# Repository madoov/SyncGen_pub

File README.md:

# SyncGen_pub
Outlay sync generator

OUTLAW ビデオ信号ジェネレータの公開用リポジトリです。
昔のパソコン・ゲーム機・アーケード基板の映像信号のタイミングを、ドットクロックから同期の形まで設定して出力する、Efinix Trion T20Q144 の基板です。

## 中身

| フォルダ | 内容 |
| --- | --- |
| `rtl/` | FPGA の RTL (Verilog-2001、Efinity)。トップは `video_gen_top.v`。`*.hex` は文字列・フォント・プリセットの ROM、`timing.sdc` はタイミング制約 |
| `docs/` | 取扱説明書 [`manual.md`](docs/manual.md) と PDF 版 [`SyncGen.pdf`](docs/SyncGen.pdf)、ピン配置 [`pinout.md`](docs/pinout.md) (RTL のポート ⇔ 回路図のネット ⇔ FPGA のピン) |
| `pcb/` | KiCad 10 のプロジェクト (回路図・基板) |
| `efinity/` | Efinity のプロジェクト (`OUTLAW_video_signa_gen.xml`、Interface Designer のピン設定 `.peri.xml`)。プロジェクトは RTL を `../../RTL/` から読む (Windows の Efinity 用) |

## ライセンス

BSD 3-Clause License ([`LICENSE`](LICENSE))。無保証です。

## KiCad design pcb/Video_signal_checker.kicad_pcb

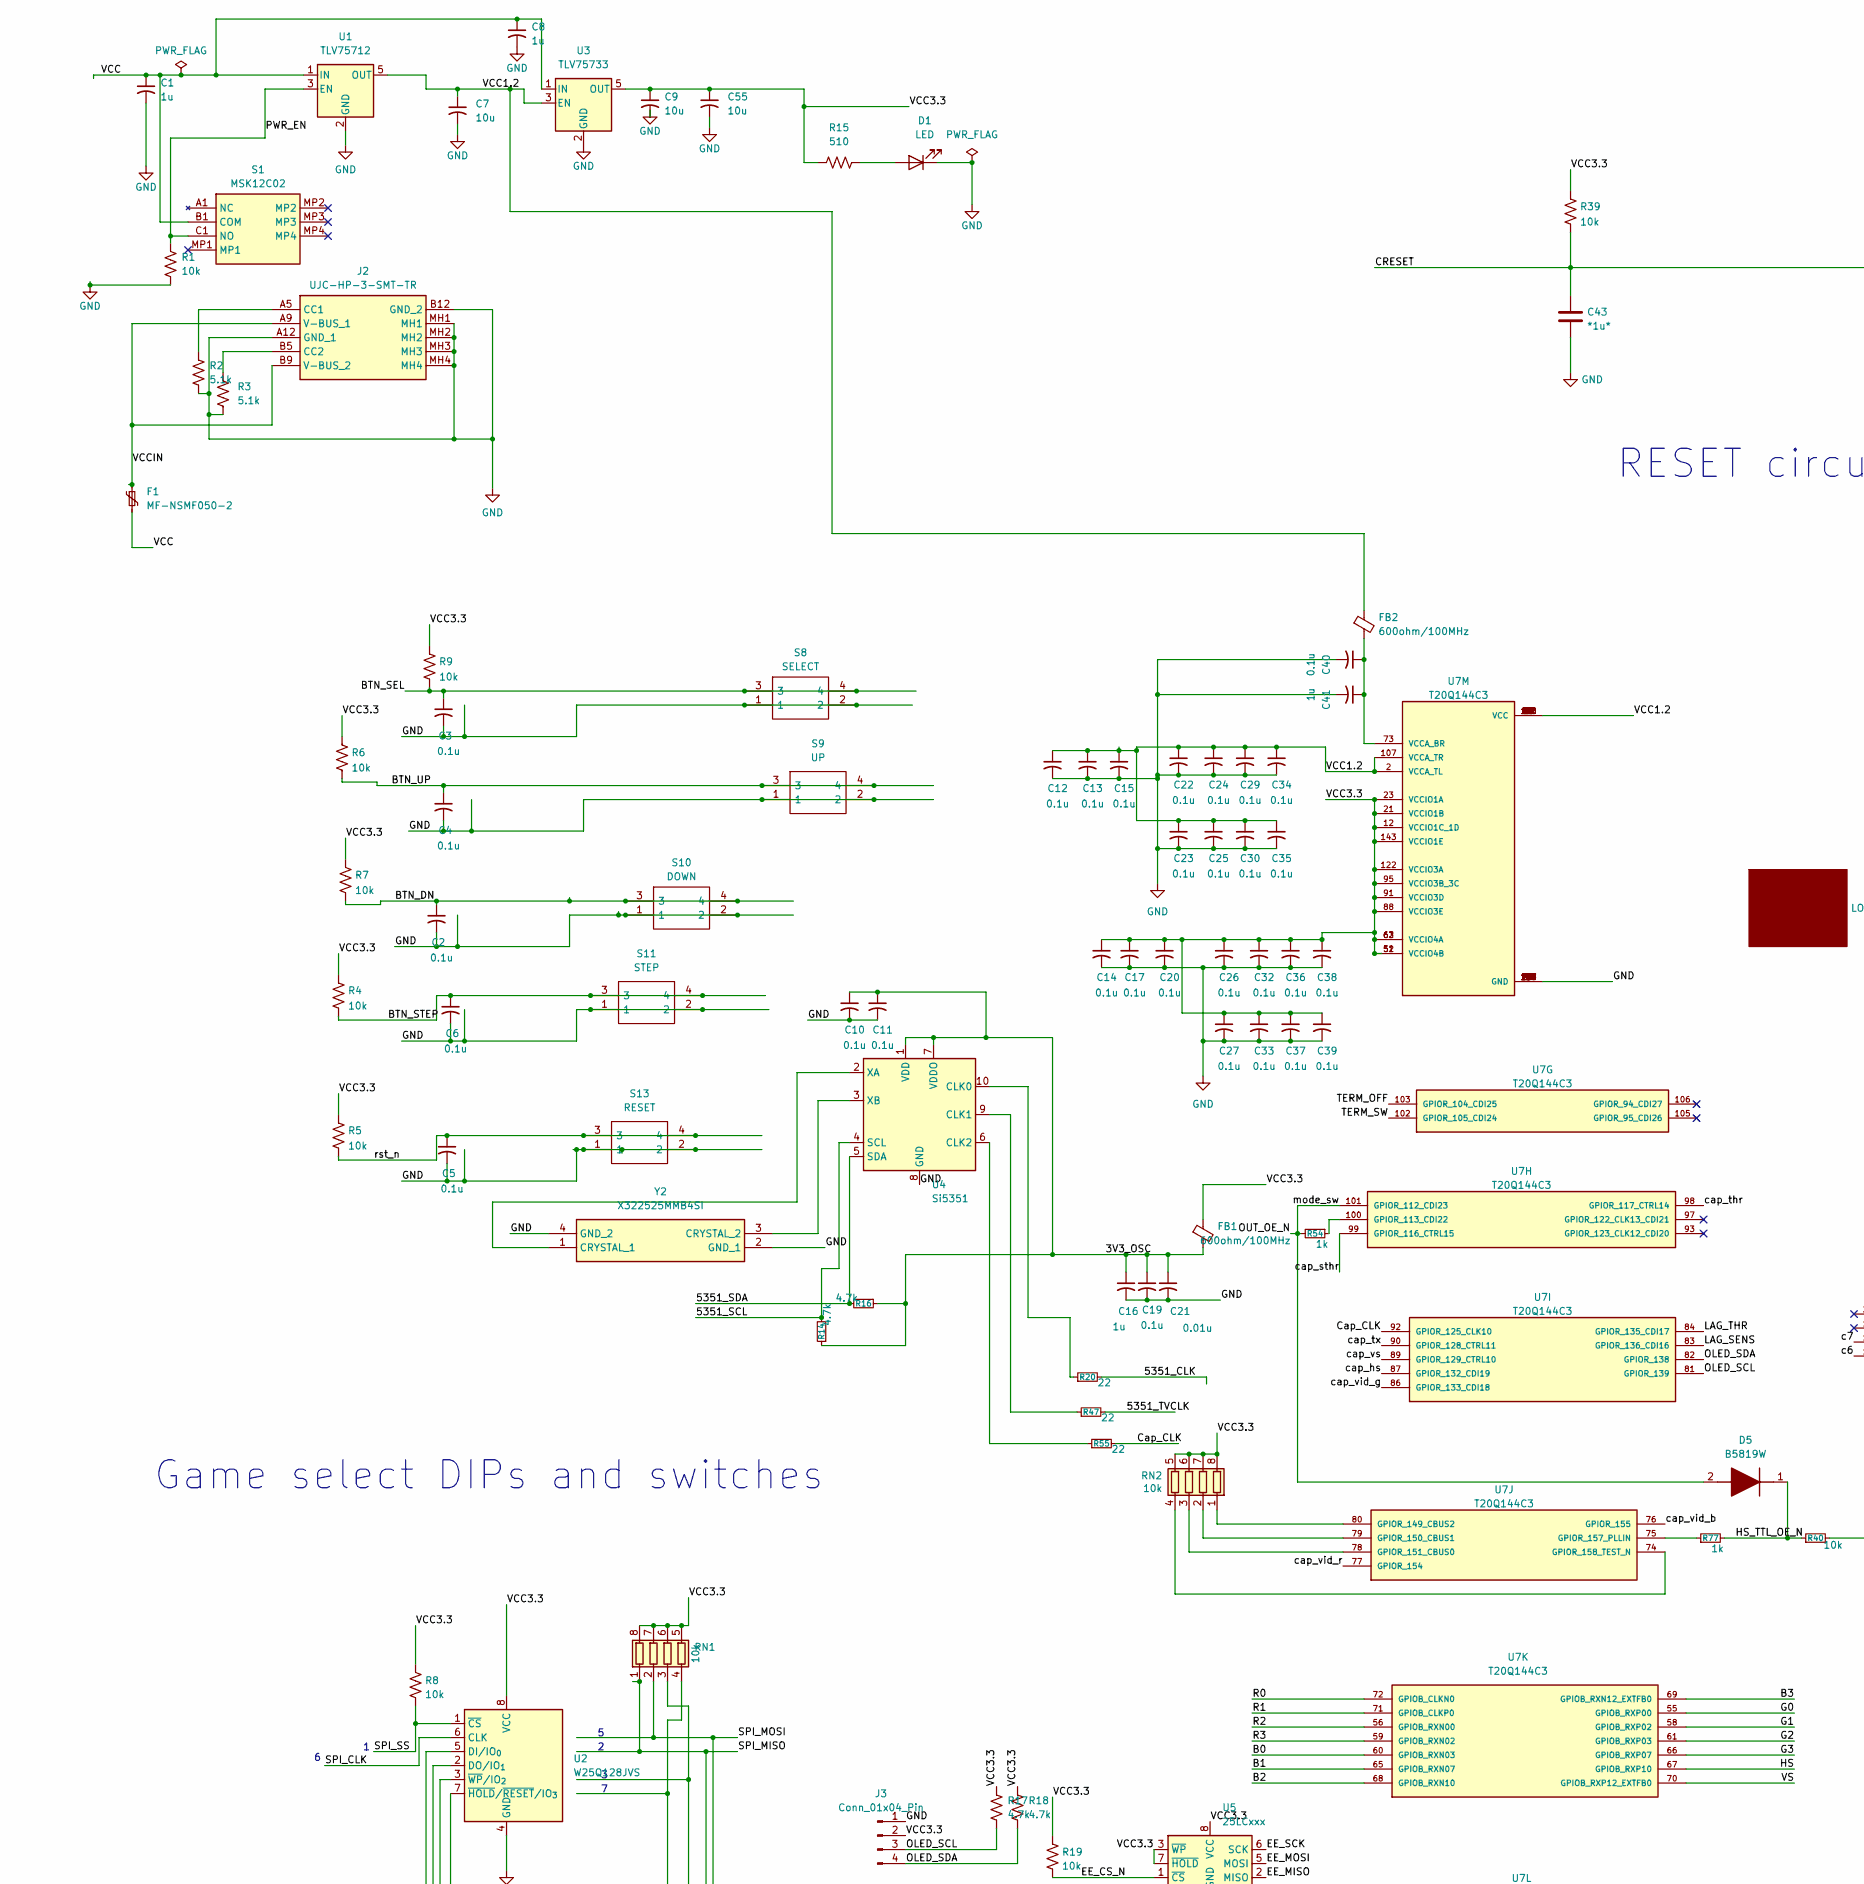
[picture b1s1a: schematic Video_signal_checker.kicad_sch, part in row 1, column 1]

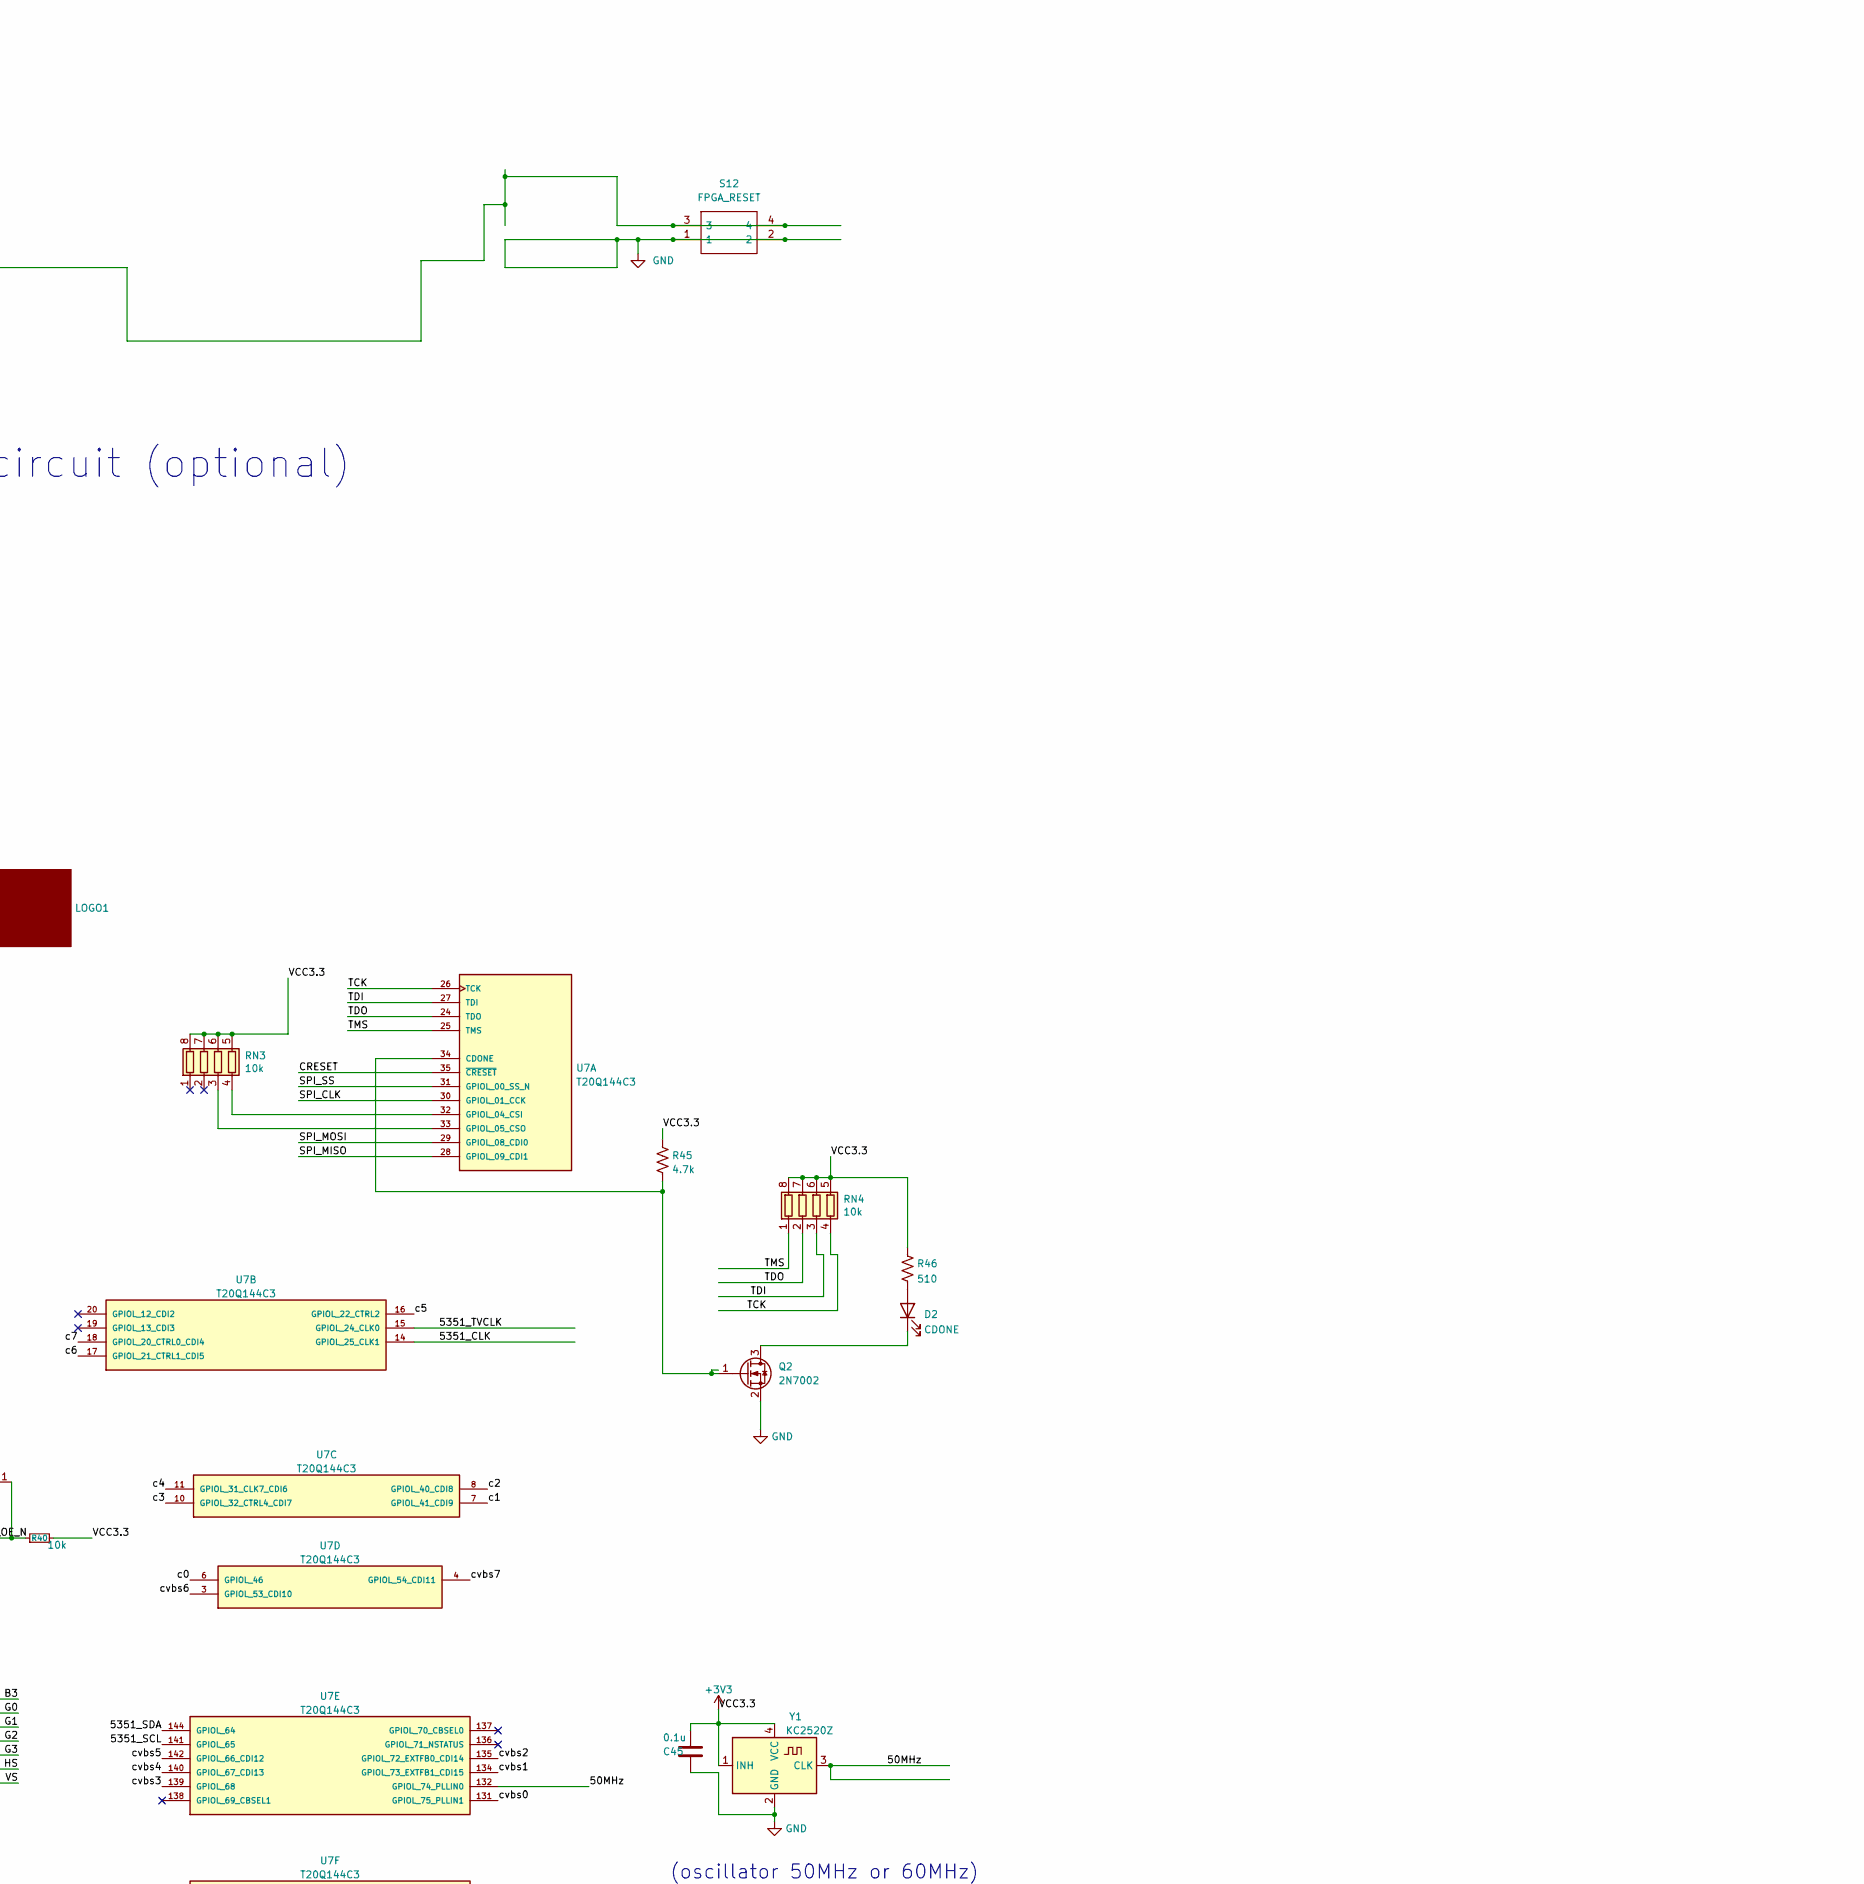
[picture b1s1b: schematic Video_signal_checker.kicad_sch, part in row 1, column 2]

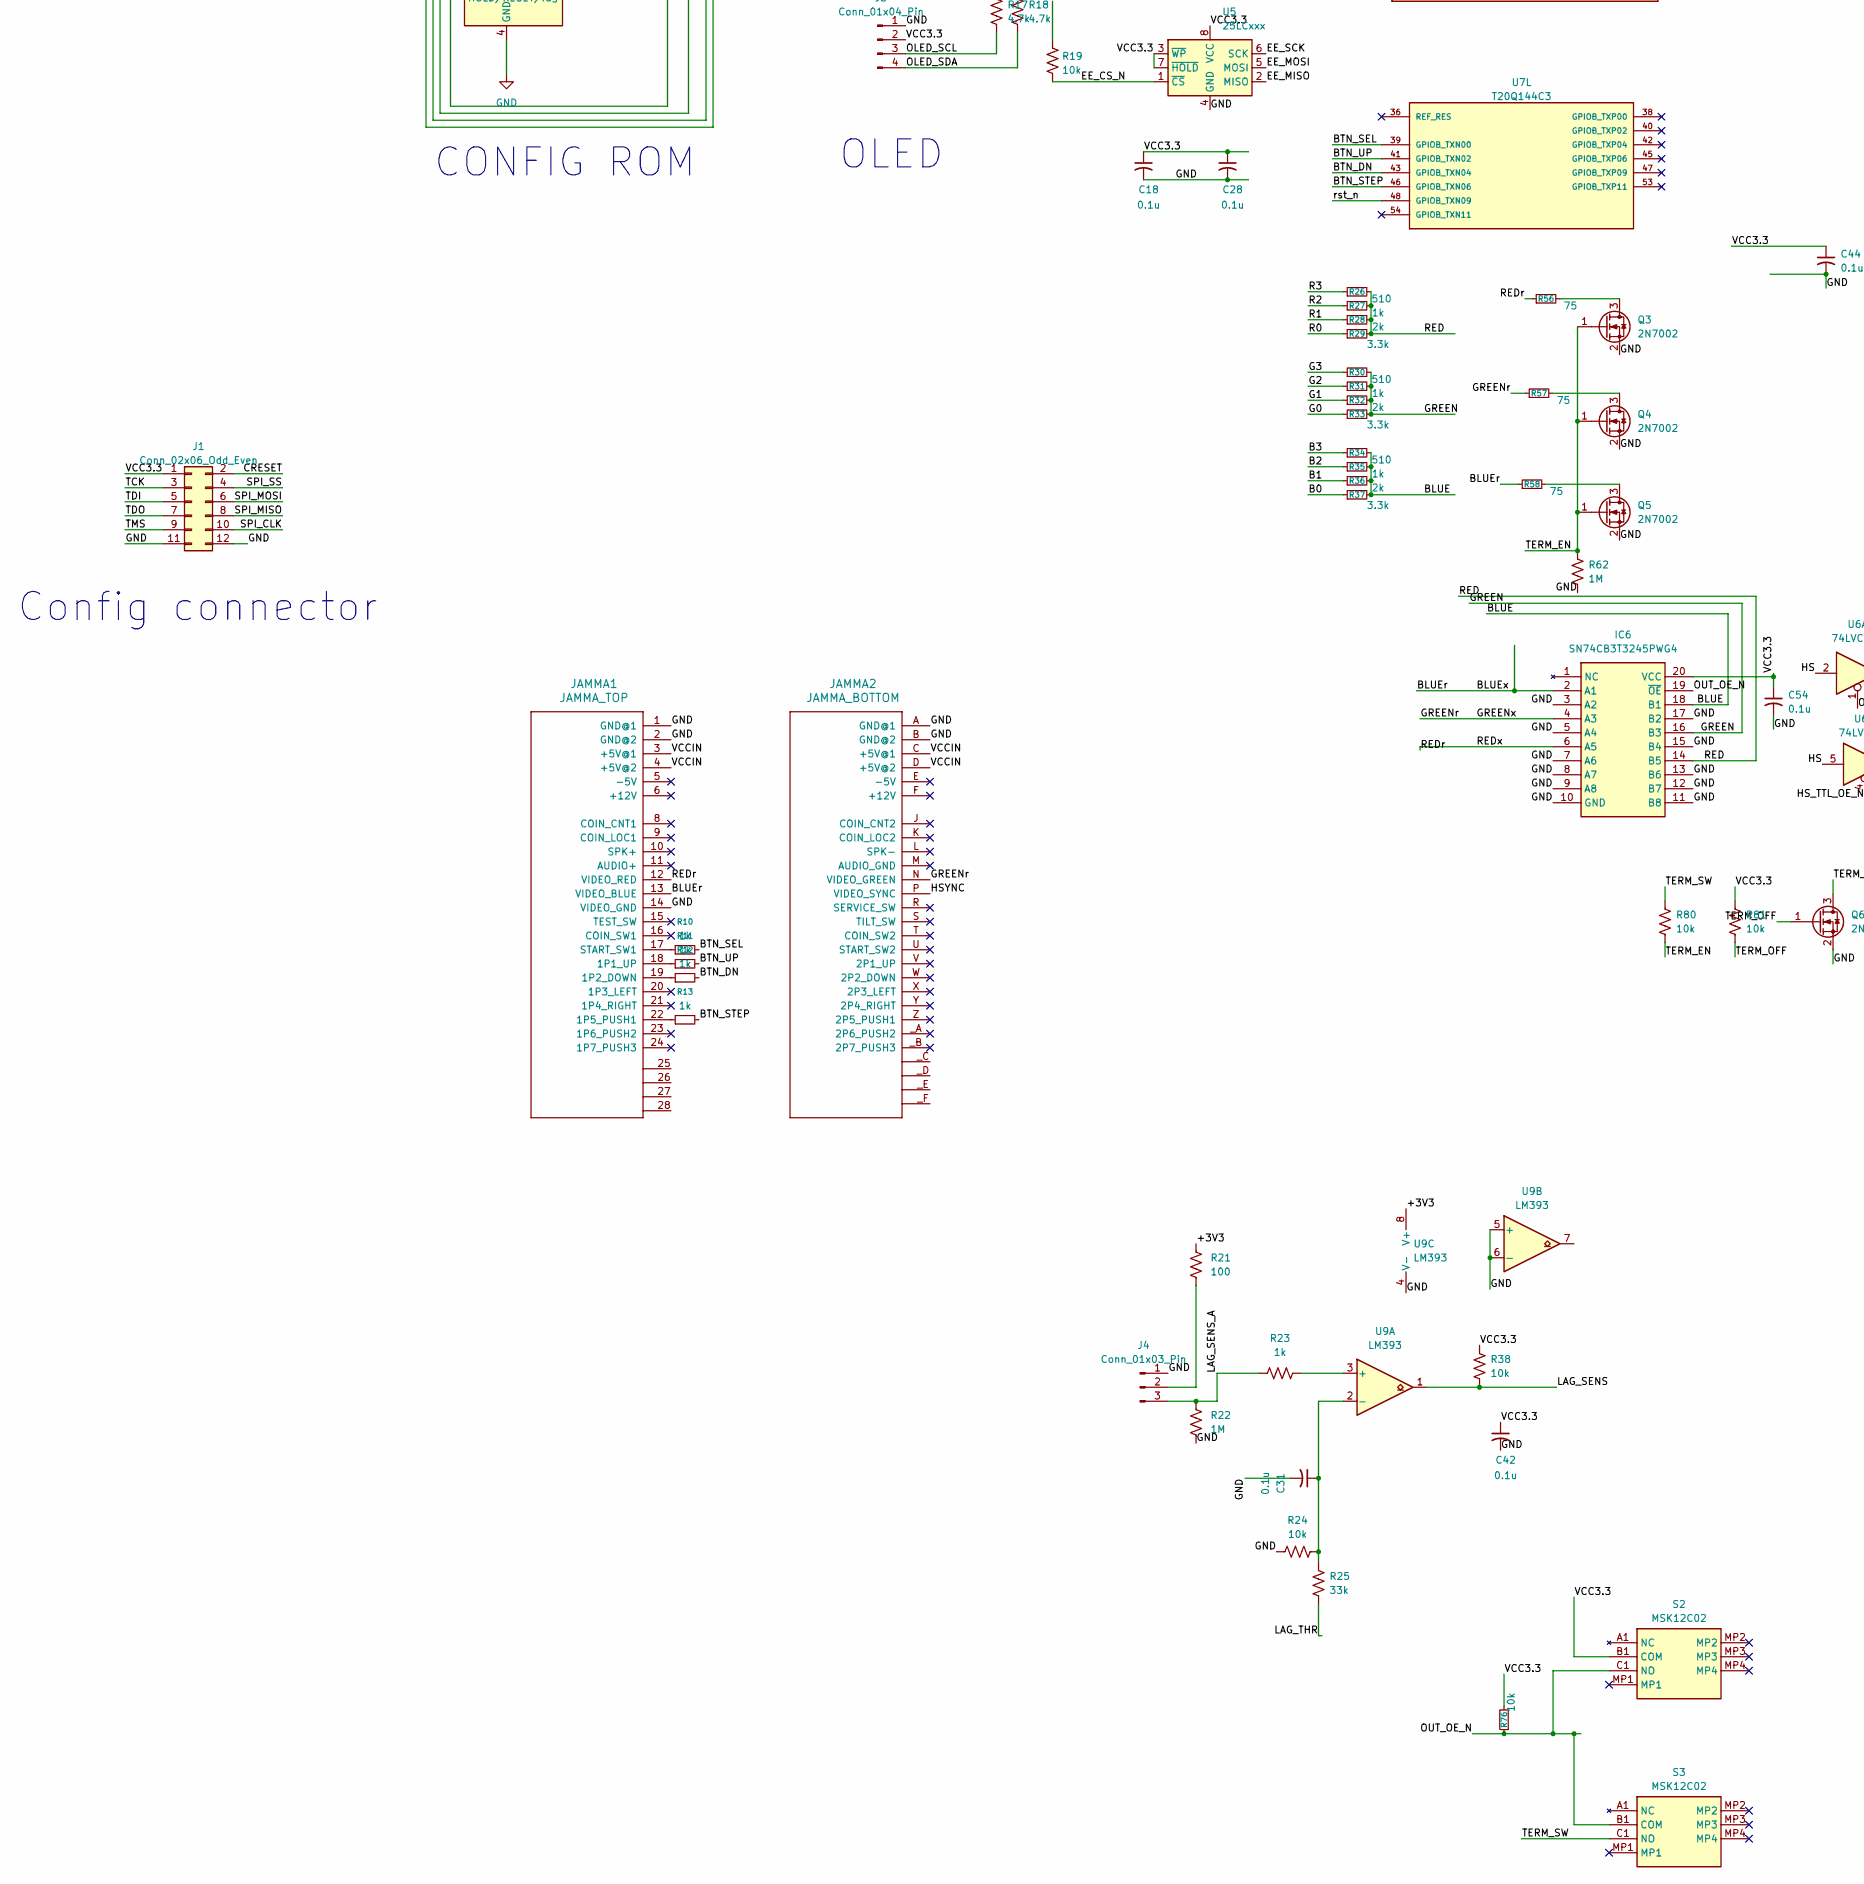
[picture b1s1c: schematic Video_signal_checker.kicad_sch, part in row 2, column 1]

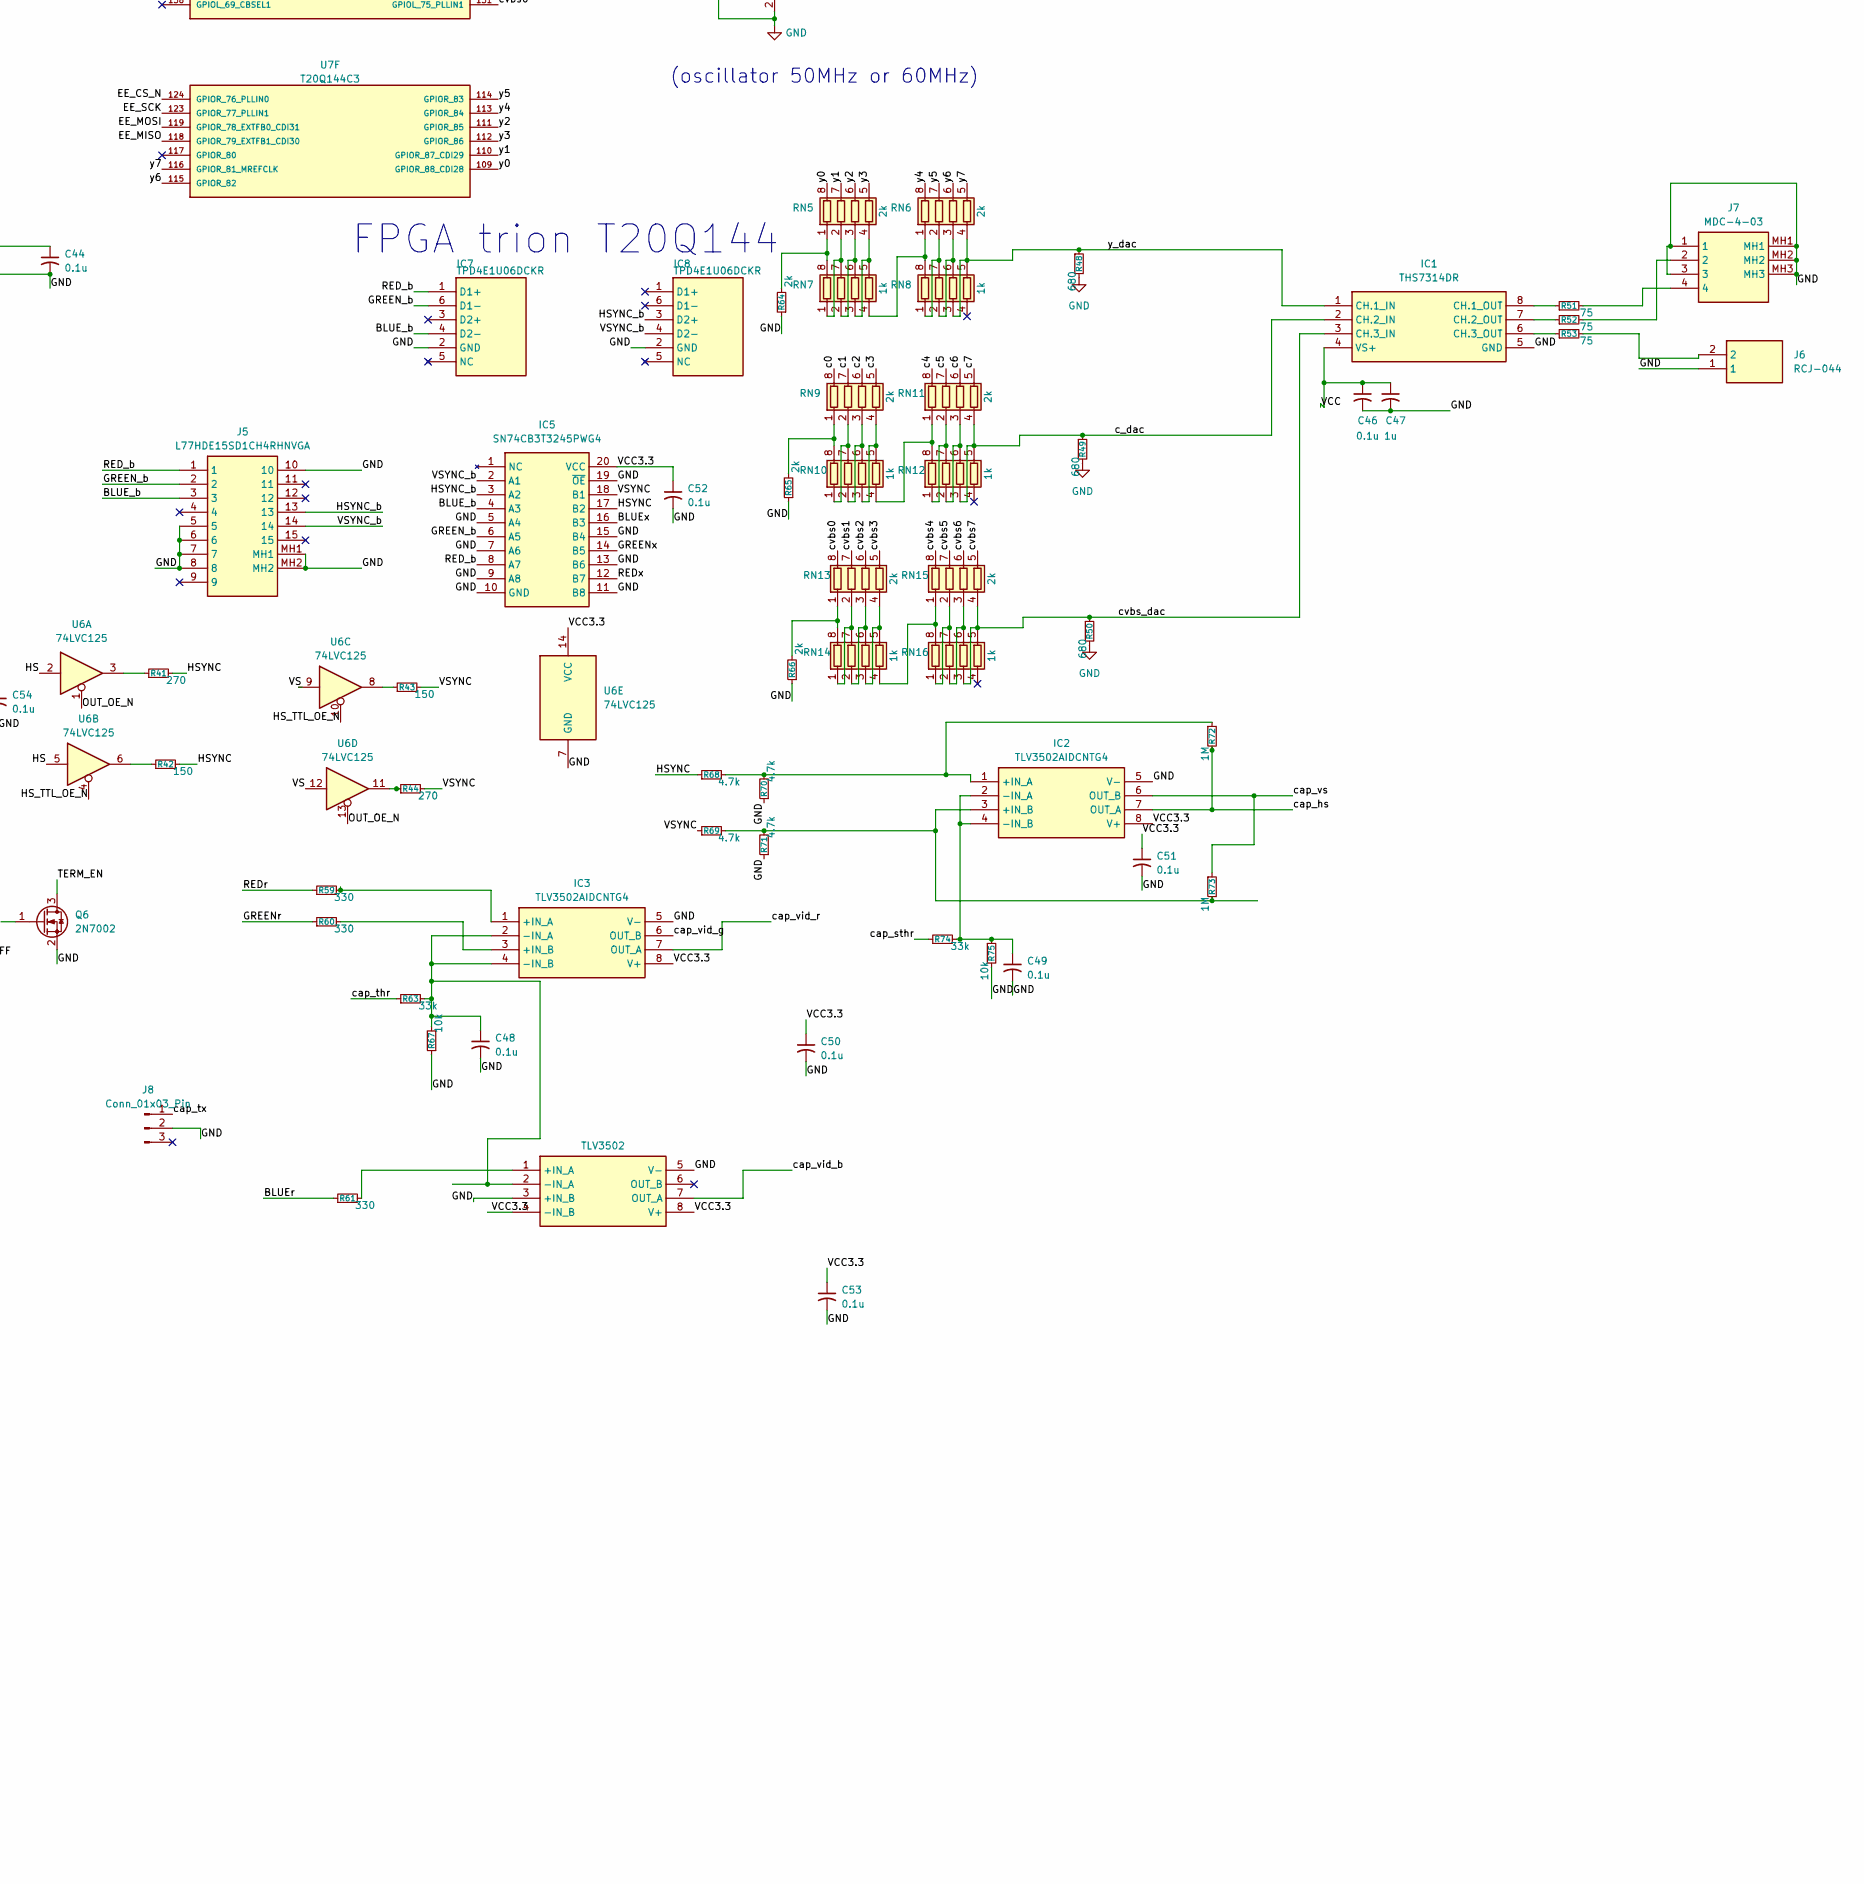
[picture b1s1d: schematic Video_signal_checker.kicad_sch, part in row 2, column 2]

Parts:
C1, C8, C16, C41, C47: 1u; C_0402_1005Metric_Pad0.74x0.62mm_HandSolder; LCSC C52923
C2, C3, C4, C5, C6, C10, C11, C12, C13, C14, C15, C17, C18, C19, C20, C22, C23, C24, C25, C26, C27, C28, C29, C30, C31, C32, C33, C34, C35, C36, C37, C38, C39, C40, C42, C44, C45, C46, C48, C49, C50, C51, C52, C53, C54: 0.1u; C_0402_1005Metric_Pad0.74x0.62mm_HandSolder; LCSC C1525
C7, C9, C55: 10u; C_0603_1608Metric_Pad1.08x0.95mm_HandSolder; LCSC C19702
C21: 0.01u; C_0402_1005Metric_Pad0.74x0.62mm_HandSolder; LCSC C15195
C43: *1u*; C_0402_1005Metric_Pad0.74x0.62mm_HandSolder; LCSC C52923
D1: LED; LED_0603_1608Metric_Pad1.05x0.95mm_HandSolder; LCSC C2286
D2: CDONE; LED_0603_1608Metric_Pad1.05x0.95mm_HandSolder; LCSC C2286
D5: B5819W; SOD3716X125N; Manufacturer_Part_Number B5819W; LCSC C8598
F1: MF-NSMF050-2; Fuse_1206_3216Metric_Pad1.42x1.75mm_HandSolder; LCSC C883126
FB1, FB2: 600ohm/100MHz; L_0603_1608Metric_Pad1.05x0.95mm_HandSolder; LCSC C1002
IC1: THS7314DR; SOIC127P600X175-8N; Manufacturer_Part_Number THS7314DR; Mouser Part Number 595-THS7314DR
IC2, IC3: TLV3502AIDCNTG4; SOT65P280X145-8N; Manufacturer_Part_Number TLV3502AIDCNTG4; Mouser Part Number 595-TLV3502AIDCNTG4
IC4: TLV3502; SOT65P280X145-8N; Manufacturer_Part_Number TLV3502AIDCNTG4; Mouser Part Number 595-TLV3502AIDCNTG4
IC5, IC6: SN74CB3T3245PWG4; SOP65P640X120-20N; Manufacturer_Part_Number SN74CB3T3245PWG4; Mouser Part Number 595-SN74CB3T3245PWG4
IC7, IC8: TPD4E1U06DCKR; SOT-363_SC-70-6; LCSC C194628
J1: Conn_02x06_Odd_Even; PinSocket_2x06_P2.54mm_Vertical
J2: UJC-HP-3-SMT-TR; UJCHP3SMTTR; Manufacturer_Part_Number UJC-HP-3-SMT-TR; Mouser Part Number 490-UJC-HP-3-SMT-TR
J3: Conn_01x04_Pin; PinSocket_1x04_P2.54mm_Vertical
J4, J8: Conn_01x03_Pin; PinHeader_1x03_P2.54mm_Vertical
J5: L77HDE15SD1CH4RHNVGA; Manufacturer_Part_Number L77HDE15SD1CH4RHNVGA; Mouser Part Number 523-7HDE15SDH4RHNVGA
J6: RCJ-044; RCJ044; Manufacturer_Part_Number RCJ-044; Mouser Part Number 490-RCJ-044
J7: MDC-4-03; MDC403; Manufacturer_Part_Number MDC-4-03
JAMMA1: JAMMA_TOP; JAMMA_TOP_10cm
JAMMA2: JAMMA_BOTTOM; JAMMA_BOTTOM_10cm
LOGO1: logo-mini
Q2, Q3, Q4, Q5, Q6: 2N7002; SOT-23; LCSC C8545
R1, R4, R5, R6, R7, R8, R9, R19, R24, R38, R39, R40, R67, R75, R76, R80, R81: 10k; R_0402_1005Metric_Pad0.72x0.64mm_HandSolder; LCSC C25744
R2, R3: 5.1k; R_0402_1005Metric_Pad0.72x0.64mm_HandSolder; LCSC C25905
R10, R11, R12, R13, R23, R27, R31, R35, R54, R77: 1k; R_0402_1005Metric_Pad0.72x0.64mm_HandSolder; LCSC C11702
R14, R16, R45, R68, R69, R70, R71: 4.7k; R_0402_1005Metric_Pad0.72x0.64mm_HandSolder; LCSC C25900
R15, R26, R30, R34, R46: 510; R_0402_1005Metric_Pad0.72x0.64mm_HandSolder; LCSC C25123
R17, R18: 4.7k; R_0603_1608Metric_Pad0.98x0.95mm_HandSolder; LCSC C25999
R20, R47, R55: 22; R_0402_1005Metric_Pad0.72x0.64mm_HandSolder; LCSC C25092
R21: 100; R_0402_1005Metric_Pad0.72x0.64mm_HandSolder; LCSC C25076
R22, R62, R72, R73: 1M; R_0402_1005Metric_Pad0.72x0.64mm_HandSolder; LCSC C26083
R25, R63, R74: 33k; R_0402_1005Metric_Pad0.72x0.64mm_HandSolder; LCSC C25779
R28, R32, R36, R64, R65, R66: 2k; R_0402_1005Metric_Pad0.72x0.64mm_HandSolder; LCSC C4109
R29, R33, R37: 3.3k; R_0402_1005Metric_Pad0.72x0.64mm_HandSolder; LCSC C25890
R41, R44: 270; R_0603_1608Metric; LCSC C22966
R42, R43: 150; R_0603_1608Metric; LCSC C22808
R48, R49, R50: 680; R_0603_1608Metric; LCSC C23228
R51, R52, R53: 75; R_0603_1608Metric; LCSC C4275
R56, R57, R58: 75; R_1206_3216Metric; LCSC C17987
R59, R60, R61: 330; R_0402_1005Metric_Pad0.72x0.64mm_HandSolder; LCSC C25104
RN1, RN2, RN3, RN4: 10k; R_Array_Convex_4x0603; LCSC C29718
RN5, RN6, RN9, RN11, RN13, RN15: 2k; R_Array_Convex_4x0603; LCSC C270875
RN7, RN8, RN10, RN12, RN14, RN16: 1k; R_Array_Convex_4x0603; LCSC C425239
S1, S2, S3: MSK12C02; Manufacturer_Part_Number MSK12C02; LCSC C431540
S8: SELECT; TL3305A-3d; Manufacturer_Part_Number TL3305AF260QG; LCSC C2886899
S9: UP; TL3305A-3d; Manufacturer_Part_Number TL3305AF260QG; LCSC C2886899
S10: DOWN; TL3305A-3d; Manufacturer_Part_Number TL3305AF260QG; LCSC C2886899
S11: STEP; TL3305A-3d; Manufacturer_Part_Number TL3305AF260QG; LCSC C2886899
S12: FPGA_RESET; TL3305A-3d; Manufacturer_Part_Number TL3305AF260QG; LCSC C2886899
S13: RESET; TL3305A-3d; Manufacturer_Part_Number TL3305AF260QG; LCSC C2886899
U1: TLV75712; SOT-23-5
U2: W25Q128JVS; SOIC-8_5.3x5.3mm_P1.27mm; LCSC C97521
U3: TLV75733; SOT-23-5; LCSC C485517
U4: Si5351; MSOP-10_3x3mm_P0.5mm; LCSC C529366
U5: 25LCxxx; SO-8_3.9x4.9mm_P1.27mm; LCSC C615820
U6: 74LVC125; TSSOP-14_4.4x5mm_P0.65mm; LCSC C7813
U7: T20Q144C3; QFP50P2200X2200X160-144N; PARTREV V3.6
U9: LM393; SOIC-8_3.9x4.9mm_P1.27mm; LCSC C7955
Y1: KC2520Z; Oscillator_SMD_Kyocera_KC2520Z-4Pin_2.5x2.0mm
Y2: X322525MMB4SI; Manufacturer_Part_Number X322525MMB4SI; LCSC C70582

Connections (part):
+3V3: C9.1, C14.1, C17.1, C18.1, C20.1, C26.1, C27.1, C28.1, C32.1, C33.1, C36.1, C37.1, C38.1, C39.1, C42.1, C44.1, C45.1, C50.1, C51.1, C52.1, C53.1, C54.1, C55.1, FB1.1, IC2.8 (V+), IC3.8 (V+), IC4.4 (-IN_B), IC4.8 (V+), IC5.20 (VCC), IC6.20 (VCC), J1.1, J3.2, R4.1, R5.1, R6.1, R7.1, R8.1, R9.1, R15.1, R17.1, R18.1, R19.1, R21.2, R38.2, R39.1, R40.2, R45.1, R46.1, R76.2, R81.1, RN1.5 (R4.2), RN1.6 (R3.2), RN1.7 (R2.2), RN1.8 (R1.2), RN2.5 (R4.2), RN2.6 (R3.2), RN2.7 (R2.2), RN2.8 (R1.2), RN3.5 (R4.2), RN3.6 (R3.2), RN3.7 (R2.2), RN3.8 (R1.2), RN4.5 (R4.2), RN4.6 (R3.2), RN4.7 (R2.2), RN4.8 (R1.2), S2.B1 (COM), U2.8 (VCC), U3.5 (OUT), U5.3 (~WP), U5.7 (~HOLD), U5.8 (VCC), U6.14 (VCC), U7.12 (VCCIO1C_1D), U7.21 (VCCIO1B), U7.23 (VCCIO1A), U7.51 (VCCIO4B), U7.52 (VCCIO4B), U7.62 (VCCIO4A), U7.63 (VCCIO4A), U7.88 (VCCIO3E)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
/3V3_OSC: C10.1, C11.1, C16.1, C19.1, C21.1, FB1.2, R14.1, R16.1, U4.1 (VDD), U4.7 (VDDO)
/50MHz: U7.132 (GPIOL_74_PLLIN0), Y1.3 (CLK)
/5351_CLK: R20.2, U7.14 (GPIOL_25_CLK1)
/5351_SCL: R14.2, U4.4 (SCL), U7.141 (GPIOL_65)
/5351_SDA: R16.2, U4.5 (SDA), U7.144 (GPIOL_64)
/5351_TVCLK: R47.2, U7.15 (GPIOL_24_CLK0)
/B0: R37.1, U7.60 (GPIOB_RXN03)
/B1: R36.1, U7.65 (GPIOB_RXN07)
/B2: R35.1, U7.68 (GPIOB_RXN10)
/B3: R34.1, U7.69 (GPIOB_RXN12_EXTFB0)
/BLUE: IC6.18 (B1), R34.2, R35.2, R36.2, R37.2
/BLUE_b: IC5.4 (A3), IC7.4 (D2-), J5.3
/BLUEr: IC5.16 (B3), IC6.2 (A1), JAMMA1.13 (VIDEO_BLUE), R58.1, R61.1
/BTN_DN: C2.1, R7.2, R12.2, S10.3, S10.4, U7.43 (GPIOB_TXN04)
/BTN_SEL: C3.1, R9.2, R10.2, S8.3, S8.4, U7.39 (GPIOB_TXN00)
/BTN_STEP: C6.1, R4.2, R13.2, S11.3, S11.4, U7.46 (GPIOB_TXN06)
/BTN_UP: C4.1, R6.2, R11.2, S9.3, S9.4, U7.41 (GPIOB_TXN02)
/CRESET: C43.1, J1.2, R39.2, S12.3, S12.4, U7.35 (~CRESET)
/Cap_CLK: R55.2, U7.92 (GPIOR_125_CLK10)
/EE_CS_N: R19.2, U5.1 (~CS), U7.124 (GPIOR_76_PLLIN0)
/EE_MISO: U5.2 (MISO), U7.118 (GPIOR_79_EXTFB1_CDI30)
/EE_MOSI: U5.5 (MOSI), U7.119 (GPIOR_78_EXTFB0_CDI31)
/EE_SCK: U5.6 (SCK), U7.123 (GPIOR_77_PLLIN1)
/G0: R33.1, U7.55 (GPIOB_RXP00)
/G1: R32.1, U7.58 (GPIOB_RXP02)
/G2: R31.1, U7.61 (GPIOB_RXP03)
/G3: R30.1, U7.66 (GPIOB_RXP07)
/GREEN: IC6.16 (B3), R30.2, R31.2, R32.2, R33.2
/GREEN_b: IC5.6 (A5), IC7.6 (D1-), J5.2
/GREENr: IC5.14 (B5), IC6.4 (A3), JAMMA2.N (VIDEO_GREEN), R57.1, R60.1
/HS: U6.2, U6.5, U7.67 (GPIOB_RXP10)
/HSYNC: IC5.17 (B2), JAMMA2.P (VIDEO_SYNC), R41.2, R42.2, R68.1
/HSYNC_b: IC5.3 (A2), IC8.3 (D2+), J5.13
/HS_TTL_OE_N: D5.1 (K), R40.1, R77.2, U6.4, U6.10
/LAG_SENS: R38.1, U7.83 (GPIOR_136_CDI16), U9.1
/LAG_SENS_A: J4.3, R22.2, R23.1
/LAG_THR: R25.1, U7.84 (GPIOR_135_CDI17)
/OLED_SCL: J3.3, R17.2, U7.81 (GPIOR_139)
/OLED_SDA: J3.4, R18.2, U7.82 (GPIOR_138)
/OUT_OE_N: D5.2 (A), IC6.19 (~OE), R54.2, R76.1, S2.C1 (NO), S3.B1 (COM), U6.1, U6.13, U7.101 (GPIOR_112_CDI23)
/PWR_EN: R1.1, S1.C1 (NO), U1.3 (EN)
/R0: R29.1, U7.72 (GPIOB_CLKN0)
/R1: R28.1, U7.71 (GPIOB_CLKP0)
/R2: R27.1, U7.56 (GPIOB_RXN00)
/R3: R26.1, U7.59 (GPIOB_RXN02)
/RED: IC6.14 (B5), R26.2, R27.2, R28.2, R29.2
/RED_b: IC5.8 (A7), IC7.1 (D1+), J5.1
/REDr: IC5.12 (B7), IC6.6 (A5), JAMMA1.12 (VIDEO_RED), R56.1, R59.1
/SPI_CLK: J1.10, U2.6 (CLK), U7.30 (GPIOL_01_CCK)
/SPI_MISO: J1.8, RN1.1 (R1.1), U2.2 (DO/IO_{1}), U7.28 (GPIOL_09_CDI1)
/SPI_MOSI: J1.6, RN1.2 (R2.1), U2.5 (DI/IO_{0}), U7.29 (GPIOL_08_CDI0)
/SPI_SS: J1.4, R8.2, U2.1 (~CS), U7.31 (GPIOL_00_SS_N)
/TCK: J1.3, RN4.4 (R4.1), U7.26 (TCK)
/TDI: J1.5, RN4.3 (R3.1), U7.27 (TDI)
/TDO: J1.7, RN4.2 (R2.1), U7.24 (TDO)
/TERM_EN: Q3.1 (G), Q4.1 (G), Q5.1 (G), Q6.3 (D), R62.1, R80.2
/TERM_OFF: Q6.1 (G), R81.2, U7.103 (GPIOR_104_CDI25)
/TERM_SW: R80.1, S3.C1 (NO), U7.102 (GPIOR_105_CDI24)
/TMS: J1.9, RN4.1 (R1.1), U7.25 (TMS)
/VCC: C1.1, C8.1, C46.1, C47.1, F1.2, IC1.4 (VS+), S1.B1 (COM), U1.1 (IN), U3.1 (IN)
/VCC1.2: C7.1, C12.1, C13.1, C15.1, C22.1, C23.1, C24.1, C25.1, C29.1, C30.1, C34.1, C35.1, FB2.1, U1.5 (OUT), U3.3 (EN), U7.2 (VCCA_TL), U7.13 (VCC), U7.22 (VCC), U7.49 (VCC), U7.57 (VCC), U7.85 (VCC), U7.96 (VCC), U7.107 (VCCA_TR), U7.125 (VCC), U7.128 (VCC), U7.130 (VCC)
/VCCIN: F1.1, J2.A9 (V-BUS_1), J2.B9 (V-BUS_2), JAMMA1.3 (+5V@1), JAMMA1.4 (+5V@2), JAMMA2.C (+5V@1), JAMMA2.D (+5V@2)
/VS: U6.9, U6.12, U7.70 (GPIOB_RXP12_EXTFB0)
/VSYNC: IC5.18 (B1), R43.2, R44.2, R69.1
/VSYNC_b: IC5.2 (A1), IC8.4 (D2-), J5.14
/c0: RN9.8 (R1.2), U7.6 (GPIOL_46)
/c1: RN9.7 (R2.2), U7.7 (GPIOL_41_CDI9)
/c2: RN9.6 (R3.2), U7.8 (GPIOL_40_CDI8)
/c3: RN9.5 (R4.2), U7.10 (GPIOL_32_CTRL4_CDI7)
/c4: RN11.8 (R1.2), U7.11 (GPIOL_31_CLK7_CDI6)
/c5: RN11.7 (R2.2), U7.16 (GPIOL_22_CTRL2)
/c6: RN11.6 (R3.2), U7.17 (GPIOL_21_CTRL1_CDI5)
/c7: RN11.5 (R4.2), U7.18 (GPIOL_20_CTRL0_CDI4)
/c_dac: IC1.2 (CH.2_IN), R49.1, RN11.4 (R4.1), RN12.3 (R3.1), RN12.5 (R4.2)
/cap_hs: IC2.7 (OUT_A), R72.2, U7.87 (GPIOR_132_CDI19)
/cap_sthr: R74.1, U7.99 (GPIOR_116_CTRL15)
/cap_thr: R63.1, U7.98 (GPIOR_117_CTRL14)
/cap_tx: J8.1, U7.90 (GPIOR_128_CTRL11)
/cap_vid_b: IC4.7 (OUT_A), U7.76 (GPIOR_155)
/cap_vid_g: IC3.6 (OUT_B), U7.86 (GPIOR_133_CDI18)
/cap_vid_r: IC3.7 (OUT_A), U7.77 (GPIOR_154)
/cap_vs: IC2.6 (OUT_B), R73.1, U7.89 (GPIOR_129_CTRL10)
/cvbs0: RN13.8 (R1.2), U7.131 (GPIOL_75_PLLIN1)
/cvbs1: RN13.7 (R2.2), U7.134 (GPIOL_73_EXTFB1_CDI15)
/cvbs2: RN13.6 (R3.2), U7.135 (GPIOL_72_EXTFB0_CDI14)
/cvbs3: RN13.5 (R4.2), U7.139 (GPIOL_68)
/cvbs4: RN15.8 (R1.2), U7.140 (GPIOL_67_CDI13)
/cvbs5: RN15.7 (R2.2), U7.142 (GPIOL_66_CDI12)
/cvbs6: RN15.6 (R3.2), U7.3 (GPIOL_53_CDI10)
/cvbs7: RN15.5 (R4.2), U7.4 (GPIOL_54_CDI11)
/cvbs_dac: IC1.3 (CH.3_IN), R50.1, RN15.4 (R4.1), RN16.3 (R3.1), RN16.5 (R4.2)
/rst_n: C5.1, R5.2, S13.3, S13.4, U7.48 (GPIOB_TXN09)
/y0: RN5.8 (R1.2), U7.109 (GPIOR_88_CDI28)
/y1: RN5.7 (R2.2), U7.110 (GPIOR_87_CDI29)
/y2: RN5.6 (R3.2), U7.111 (GPIOR_85)
/y3: RN5.5 (R4.2), U7.112 (GPIOR_86)
/y4: RN6.8 (R1.2), U7.113 (GPIOR_84)
/y5: RN6.7 (R2.2), U7.114 (GPIOR_83)
/y6: RN6.6 (R3.2), U7.115 (GPIOR_82)
/y7: RN6.5 (R4.2), U7.116 (GPIOR_81_MREFCLK)
/y_dac: IC1.1 (CH.1_IN), R48.1, RN6.4 (R4.1), RN8.3 (R3.1), RN8.5 (R4.2)
GND: C1.2, C2.2, C3.2, C4.2, C5.2, C6.2, C7.2, C8.2, C9.2, C10.2, C11.2, C12.2, C13.2, C14.2, C15.2, C16.2, C17.2, C18.2, C19.2, C20.2, C21.2, C22.2, C23.2, C24.2, C25.2, C26.2, C27.2, C28.2, C29.2, C30.2, C31.2, C32.2, C33.2, C34.2, C35.2, C36.2, C37.2, C38.2, C39.2, C40.2, C41.2, C42.2, C43.2, C44.2, C45.2, C46.2, C47.2, C48.2, C49.2, C50.2, C51.2, C52.2, C53.2, C54.2, C55.2, D1.1 (K), IC1.5 (GND), IC2.5 (V-), IC3.5 (V-), IC4.3 (+IN_B), IC4.5 (V-), IC5.5 (A4), IC5.7 (A6), IC5.9 (A8), IC5.10 (GND), IC5.11 (B8), IC5.13 (B6), IC5.15 (B4), IC5.19 (~OE), IC6.3 (A2), IC6.5 (A4), IC6.7 (A6), IC6.8 (A7), IC6.9 (A8), IC6.10 (GND), IC6.11 (B8), IC6.12 (B7), IC6.13 (B6), IC6.15 (B4), IC6.17 (B2), IC7.2 (GND)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
unnamed: D1.2 (A), R15.2
unnamed: D2.2 (A), R46.2
unnamed: D2.1 (K), Q2.3 (D)
unnamed: IC1.8 (CH.1_OUT), R51.1
unnamed: IC1.7 (CH.2_OUT), R52.1
unnamed: IC1.6 (CH.3_OUT), R53.1
unnamed: IC2.1 (+IN_A), R68.2, R70.2, R72.1
unnamed: IC2.3 (+IN_B), R69.2, R71.2, R73.2
unnamed: C49.1, IC2.2 (-IN_A), IC2.4 (-IN_B), R74.2, R75.1
unnamed: IC3.1 (+IN_A), R59.2
unnamed: IC3.3 (+IN_B), R60.2
unnamed: C48.1, IC3.2 (-IN_A), IC3.4 (-IN_B), IC4.2 (-IN_A), R63.2, R67.2
unnamed: IC4.1 (+IN_A), R61.2
unnamed: J2.A5 (CC1), R2.1
unnamed: J2.B5 (CC2), R3.1
unnamed: J4.2, R21.1
unnamed: J6.2, R53.2
unnamed: J7.2, R52.2
unnamed: J7.4, R51.2
unnamed: JAMMA1.18 (1P1_UP), R11.1
unnamed: JAMMA1.19 (1P2_DOWN), R12.1
unnamed: JAMMA1.22 (1P5_PUSH1), R13.1
unnamed: JAMMA1.17 (START_SW1), R10.1
unnamed: Q2.1 (G), R45.2, U7.34 (CDONE)
unnamed: Q3.3 (D), R56.2
unnamed: Q4.3 (D), R57.2
unnamed: Q5.3 (D), R58.2
unnamed: R41.1, U6.3
unnamed: R42.1, U6.6
unnamed: R43.1, U6.8
unnamed: R44.1, U6.11
unnamed: RN1.3 (R3.1), U2.3 (~WP/IO_{2})
unnamed: RN1.4 (R4.1), U2.7 (~HOLD/~RESET/IO_{3})
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
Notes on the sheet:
Game select DIPs and switches
Config connector
FPGA trion T20Q144
RESET circuit (optional)
CONFIG ROM
(oscillator 50MHz or 60MHz)
OLED

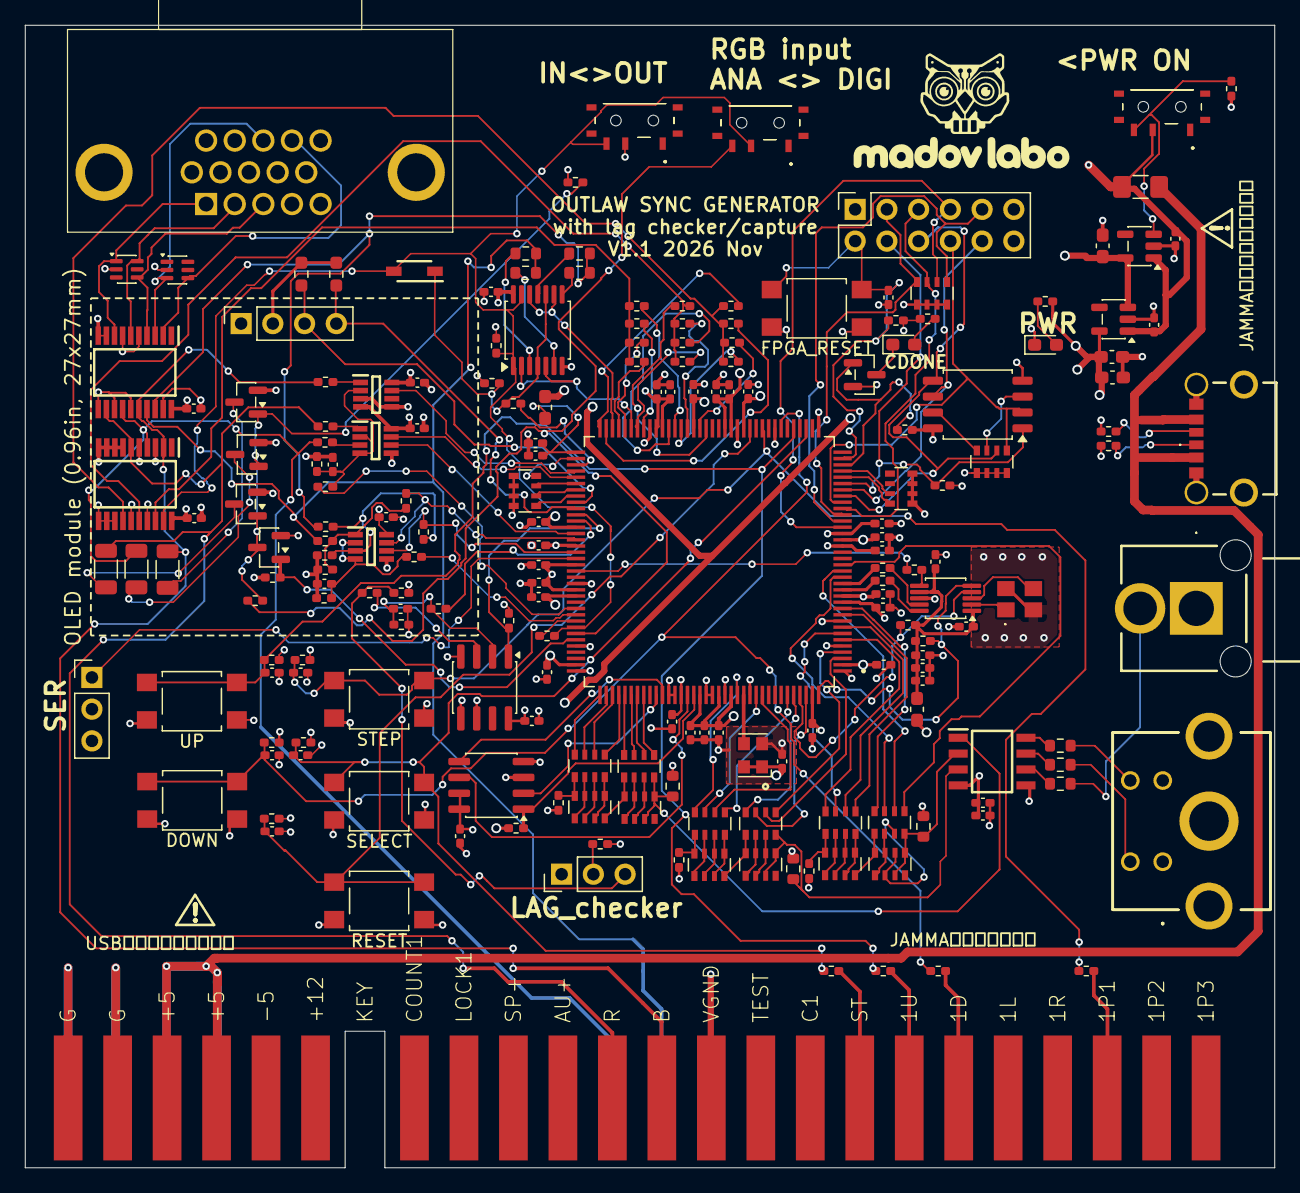
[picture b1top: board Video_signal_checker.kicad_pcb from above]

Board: 4 copper layers, 100.0 x 91.4 mm, 199 parts (0 on the bottom side), 173 nets.
